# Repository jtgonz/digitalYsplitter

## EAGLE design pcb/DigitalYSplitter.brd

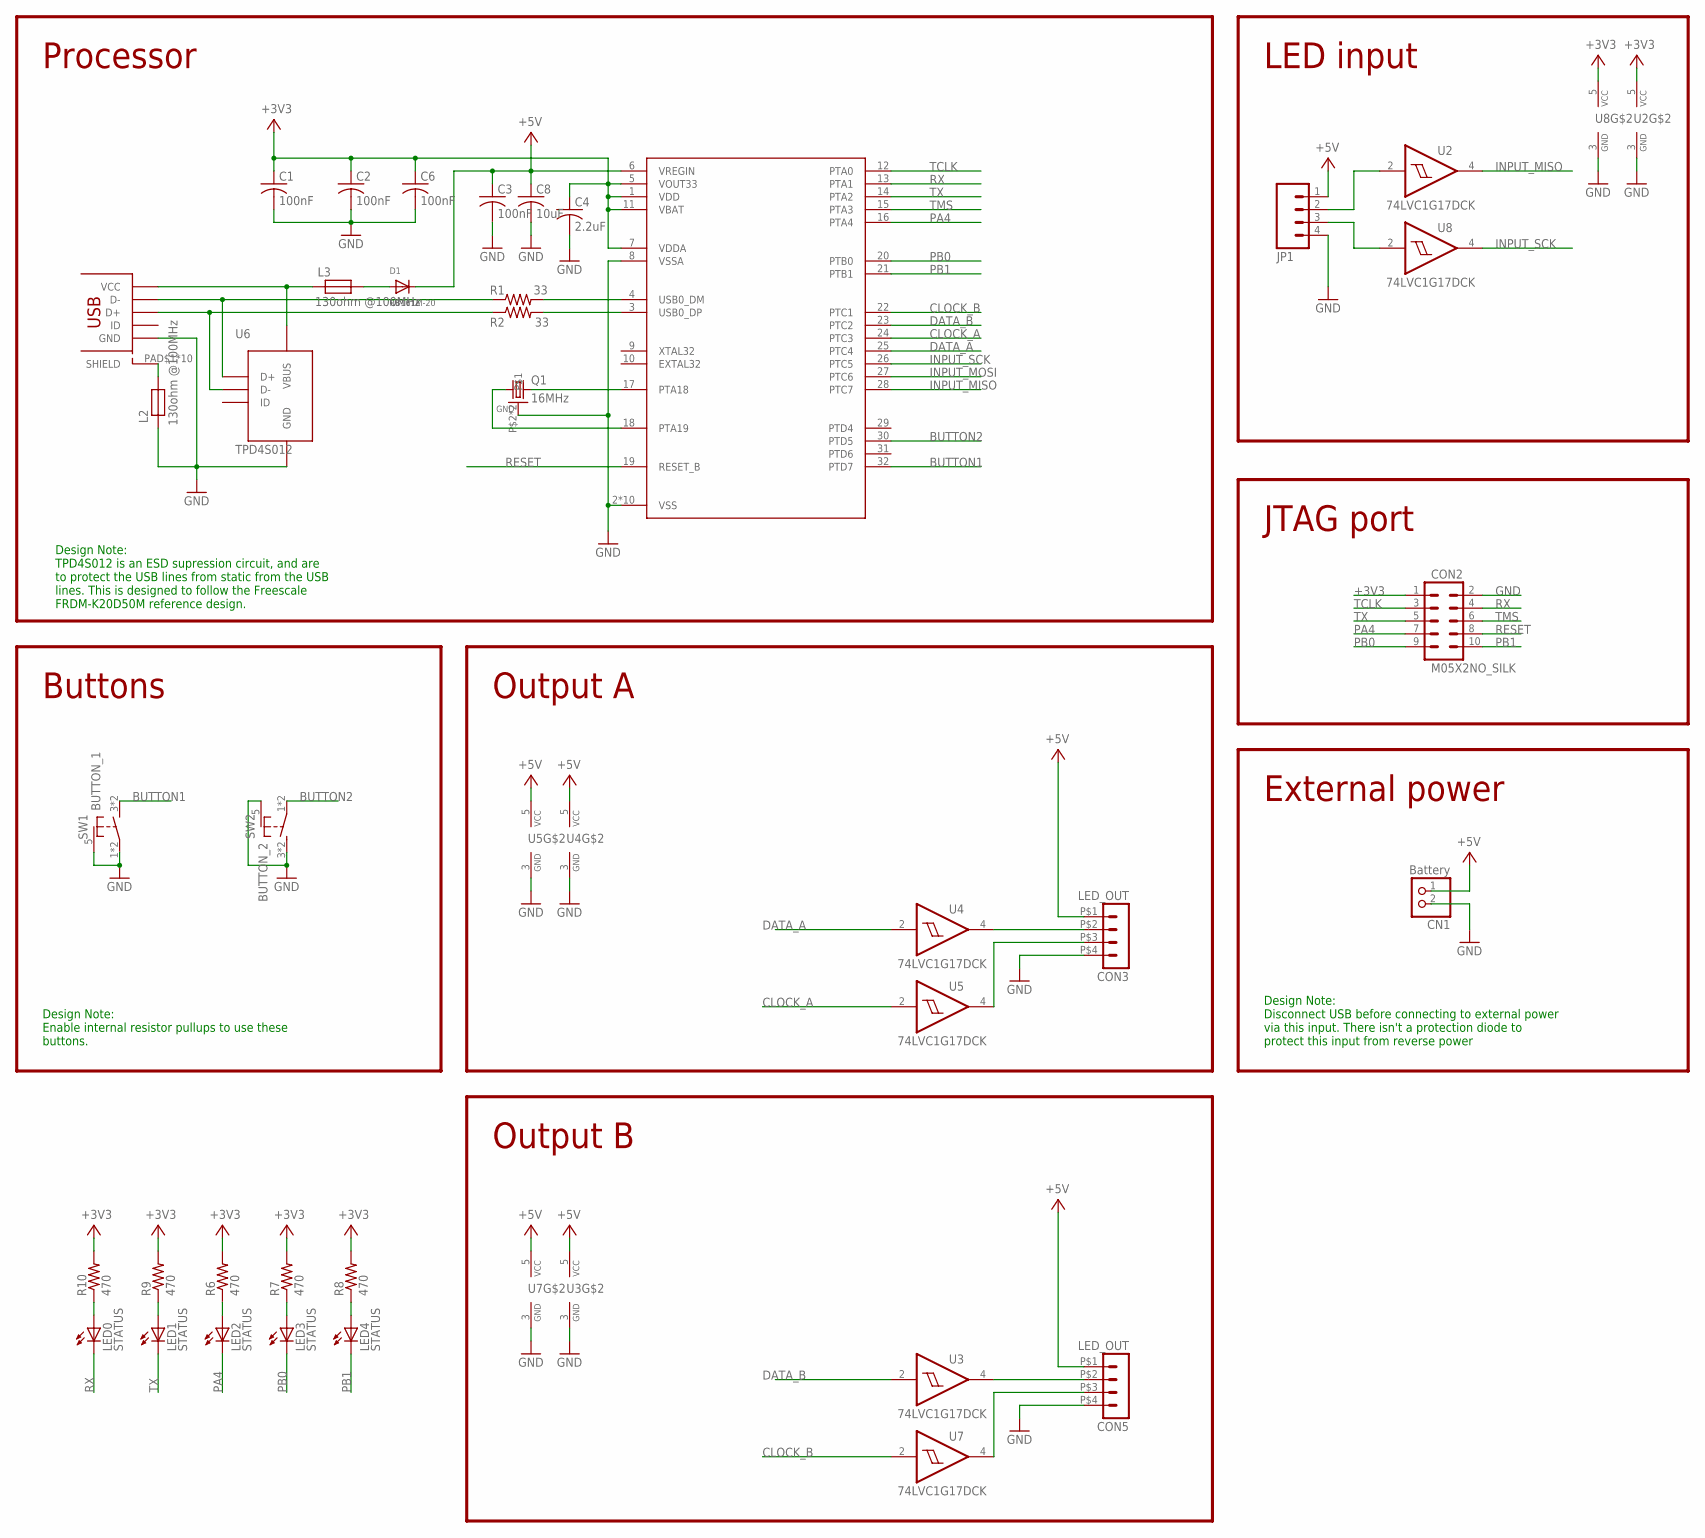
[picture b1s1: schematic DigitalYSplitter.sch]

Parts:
C1, C2, C3, C6: 100nF; C0402
C4: 2.2uF; C0402
C8: 10uF; C0805K
CN1: Battery; JST-PH-2-THM-RA
CON1: USB_MICROSMT+THRUHULE; USB_MICRO_THRUHOLE
CON2: M05X2NO_SILK; 2X5_NOSILK
CON3, CON5: LED_OUT; DUPONT-4P
D1: RB161M-20; SOD-123
JP1: M04PTH; 1X04
L2, L3: 130ohm @100MHz; 0805
LED0, LED1, LED2, LED3, LED4: STATUS; CHIPLED_0805
Q1: 16MHz; CRSYTAL_2520
R1, R2: 33; R0402
R6, R7, R8, R9, R10: 470; R0402
SW1: BUTTON_1; TD-07XB
SW2: BUTTON_2; TD-07XB
U1: MK20D--VFM5; QFN32_5X5_LONGLEADS
U2, U3, U4, U5, U7, U8: 74LVC1G17DCK; SC70-5
U6: TPD4S012; R-PUSON-N6

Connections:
+3V3: C1.1, C2.1, C4.1, C6.1, CON2.1, R6.2, R7.2, R8.2, R9.2, R10.2, U1.1 (VDD), U1.5 (VOUT33), U1.7 (VDDA), U1.11 (VBAT), U2.5 (VCC), U8.5 (VCC)
+5V: C3.1, C8.1, CN1.1 (2), CON3.P$1 (1), CON5.P$1 (1), D1.C, JP1.1, U1.6 (VREGIN), U3.5 (VCC), U4.5 (VCC), U5.5 (VCC), U7.5 (VCC)
BUTTON1: SW1.3 (S), SW1.4 (S), U1.32 (PTD7)
BUTTON2: SW2.1, SW2.2, U1.30 (PTD5)
CLOCK_A: U1.24 (PTC3), U5.2 (I)
CLOCK_B: U1.22 (PTC1), U7.2 (I)
DATA_A: U1.25 (PTC4), U4.2 (I)
DATA_B: U1.23 (PTC2), U3.2 (I)
GND: C1.2, C2.2, C3.2, C4.2, C6.2, C8.2, CN1.2 (1), CON1.PIN$5 (GND), CON2.2, CON3.P$4 (4), CON5.P$4 (4), JP1.4, L2.2, Q1.P$2, Q1.P$4, SW1.1, SW1.2, SW1.5 (SHIELD), SW2.3 (S), SW2.4 (S), SW2.5 (SHIELD), U1.2 (VSS), U1.8 (VSSA), U1.PAD@1 (VSS), U1.PAD@2 (VSS), U1.PAD@3 (VSS), U1.PAD@4 (VSS), U1.PAD@5 (VSS), U1.PAD@6 (VSS), U1.PAD@9 (VSS), U1.PAD@10 (VSS), U1.PAD@11 (VSS), U2.3 (GND), U3.3 (GND), U4.3 (GND), U5.3 (GND), U6.P$4 (GND), U7.3 (GND), U8.3 (GND)
INPUT_MISO: U1.28 (PTC7), U2.4 (O)
INPUT_MOSI: U1.27 (PTC6)
INPUT_SCK: U1.26 (PTC5), U8.4 (O)
LED_DATA: CON3.P$2 (2), U4.4 (O)
LED_DATA1: CON5.P$2 (2), U3.4 (O)
unnamed: Q1.P$1 (1), U1.18 (PTA19)
unnamed: Q1.P$3 (2), U1.17 (PTA18)
unnamed: CON1.PIN$1 (VCC), L3.2, U6.P$6 (VBUS)
unnamed: CON3.P$3 (3), U5.4 (O)
unnamed: CON5.P$3 (3), U7.4 (O)
unnamed: JP1.2, U2.2 (I)
unnamed: CON1.PIN$2 (D-), R1.1, U6.P$1 (D+)
unnamed: JP1.3, U8.2 (I)
unnamed: D1.A, L3.1
unnamed: CON1.PIN$3 (D+), R2.1, U6.P$2 (D-)
unnamed: R1.2, U1.4 (USB0_DM)
unnamed: R2.2, U1.3 (USB0_DP)
unnamed: LED2.A, R6.1
unnamed: LED3.A, R7.1
unnamed: LED4.A, R8.1
unnamed: LED1.A, R9.1
unnamed: LED0.A, R10.1
PA4: CON2.7, LED2.C, U1.16 (PTA4)
PB0: CON2.9, LED3.C, U1.20 (PTB0)
PB1: CON2.10, LED4.C, U1.21 (PTB1)
RESET: CON2.8, U1.19 (RESET_B)
RX: CON2.4, LED0.C, U1.13 (PTA1)
SHIELD: CON1.PAD$1 (SHIELD), CON1.PAD$2 (SHIELD), CON1.PAD$3 (SHIELD), CON1.PAD$4 (SHIELD), CON1.PAD$5 (SHIELD), CON1.PAD$6 (SHIELD), CON1.PAD$7 (SHIELD), CON1.PAD$8 (SHIELD), CON1.PAD$9 (SHIELD), CON1.PAD$10 (SHIELD), L2.1
TCLK: CON2.3, U1.12 (PTA0)
TMS: CON2.6, U1.15 (PTA3)
TX: CON2.5, LED1.C, U1.14 (PTA2)

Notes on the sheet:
Processor
LED input
Buttons
Design Note: TPD4S012 is an ESD supression circuit, and are to protect the USB lines from static from the USB lines. This is designed to follow the Freescale FRDM-K20D50M reference design.
Output A
JTAG port
External power
Design Note: Disconnect USB before connecting to external power via this input. There isn't a protection diode to protect this input from reverse power
Design Note: Enable internal resistor pullups to use these buttons.
Output B

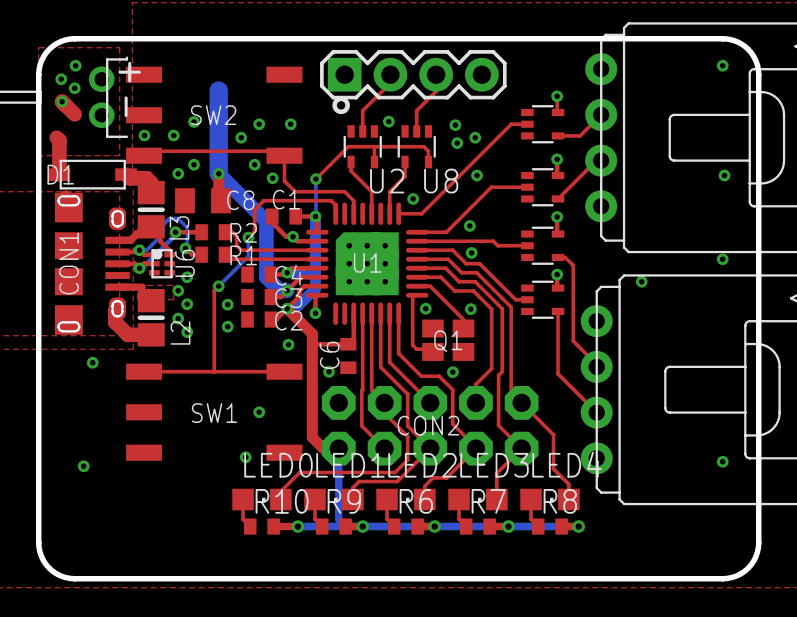
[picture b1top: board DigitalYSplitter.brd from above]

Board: 2 copper layers, 40.0 x 30.0 mm, 38 parts (0 on the bottom side), 39 nets.

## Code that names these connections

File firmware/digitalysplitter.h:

/*
 * Peripherals for the BlinkyTile controller
 *
 * Copyright (c) 2014 Matt Mets
 * 
 * Permission is hereby granted, free of charge, to any person obtaining a copy of
 * this software and associated documentation files (the "Software"), to deal in
 * the Software without restriction, including without limitation the rights to
 * use, copy, modify, merge, publish, distribute, sublicense, and/or sell copies of
 * the Software, and to permit persons to whom the Software is furnished to do so,
 * subject to the following conditions:
 * 
 * The above copyright notice and this permission notice shall be included in all
 * copies or substantial portions of the Software.
 * 
 * THE SOFTWARE IS PROVIDED "AS IS", WITHOUT WARRANTY OF ANY KIND, EXPRESS OR
 * IMPLIED, INCLUDING BUT NOT LIMITED TO THE WARRANTIES OF MERCHANTABILITY, FITNESS
 * FOR A PARTICULAR PURPOSE AND NONINFRINGEMENT. IN NO EVENT SHALL THE AUTHORS OR
 * COPYRIGHT HOLDERS BE LIABLE FOR ANY CLAIM, DAMAGES OR OTHER LIABILITY, WHETHER
 * IN AN ACTION OF CONTRACT, TORT OR OTHERWISE, ARISING FROM, OUT OF OR IN
 * CONNECTION WITH THE SOFTWARE OR THE USE OR OTHER DEALINGS IN THE SOFTWARE.
 */

#ifndef BLINKYTILE_H
#define BLINKYTILE_H

#define LED_COUNT           170  // Number of LEDs we are controlling
#define BYTES_PER_PIXEL     3

#define BUTTON_COUNT        2   // Two input buttons
#define BUTTON_A            0   // First button
#define BUTTON_B            1   // First button

#define BUTTON_A_PIN        17  // Button A: PD7
#define BUTTON_B_PIN        15  // Button B: PD5

#define DATA_IN_PIN         13  // Data input: PC7 (normally use as SPI MISO)
#define CLOCK_IN_PIN        11  // Clock input: PC5 (normally use as SPI CLK)

#define DATA_A_PIN          10  // Data output pin A: PC4
#define CLOCK_A_PIN         9   // Clock output pin A: PC3
#define DATA_B_PIN          8   // Data output pin B: PC2
#define CLOCK_B_PIN         7   // Clock output pin B: PC1

#define LED_0_PIN           1   // '30', PA1
#define LED_1_PIN           2   // '60', PA2
#define LED_2_PIN           4   // '120', PA4
#define LED_3_PIN           5   // APA102, PB0
#define LED_4_PIN           6   // WS2812, PB1

// Initialize the board hardware (buttons, status led, LED control pins)
extern void initBoard();

// Set the brightness of the status LED
// @param pin Pin that the LED is connected to
// @param value LED brightness 0 = off, 255 = on
extern void setStatusLed(uint8_t led, uint8_t value);

// Refresh the watchdog, so that the board doesn't reset
static inline void watchdog_refresh(void)
{
    __disable_irq();
    WDOG_REFRESH = 0xA602;
    WDOG_REFRESH = 0xB480;
    __enable_irq();
}

#endif

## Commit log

2015-07-03 RevA Y-splitter board
2015-07-17 Rename files, add .gitignore
2015-07-17 Bring in firmware from BlinkyTile, remove unnessecary features
2015-07-17 Small corrections to the PCB
2015-07-17 Add Teensy-based programmer from BlinkyPendant
2015-07-17 Add bootloader from blinkytile project
2015-07-17 Update bootloader to work with the LED (unsuccessful?)
2015-07-17 Small fixes to the PCB for clarity
2015-07-17 V1 bootloader
2015-07-18 Workaround to test LED outputs, button inputs.
2015-07-18 Pins seem to work!
2015-07-20 Schematic bugfix: can't use diodes for level shifting, they're too slow.

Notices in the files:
parts and their libraries:
SparkFun-Connectors: Licensing: CC v3.0 Share-Alike You are welcome to use this library for commercial purposes.
